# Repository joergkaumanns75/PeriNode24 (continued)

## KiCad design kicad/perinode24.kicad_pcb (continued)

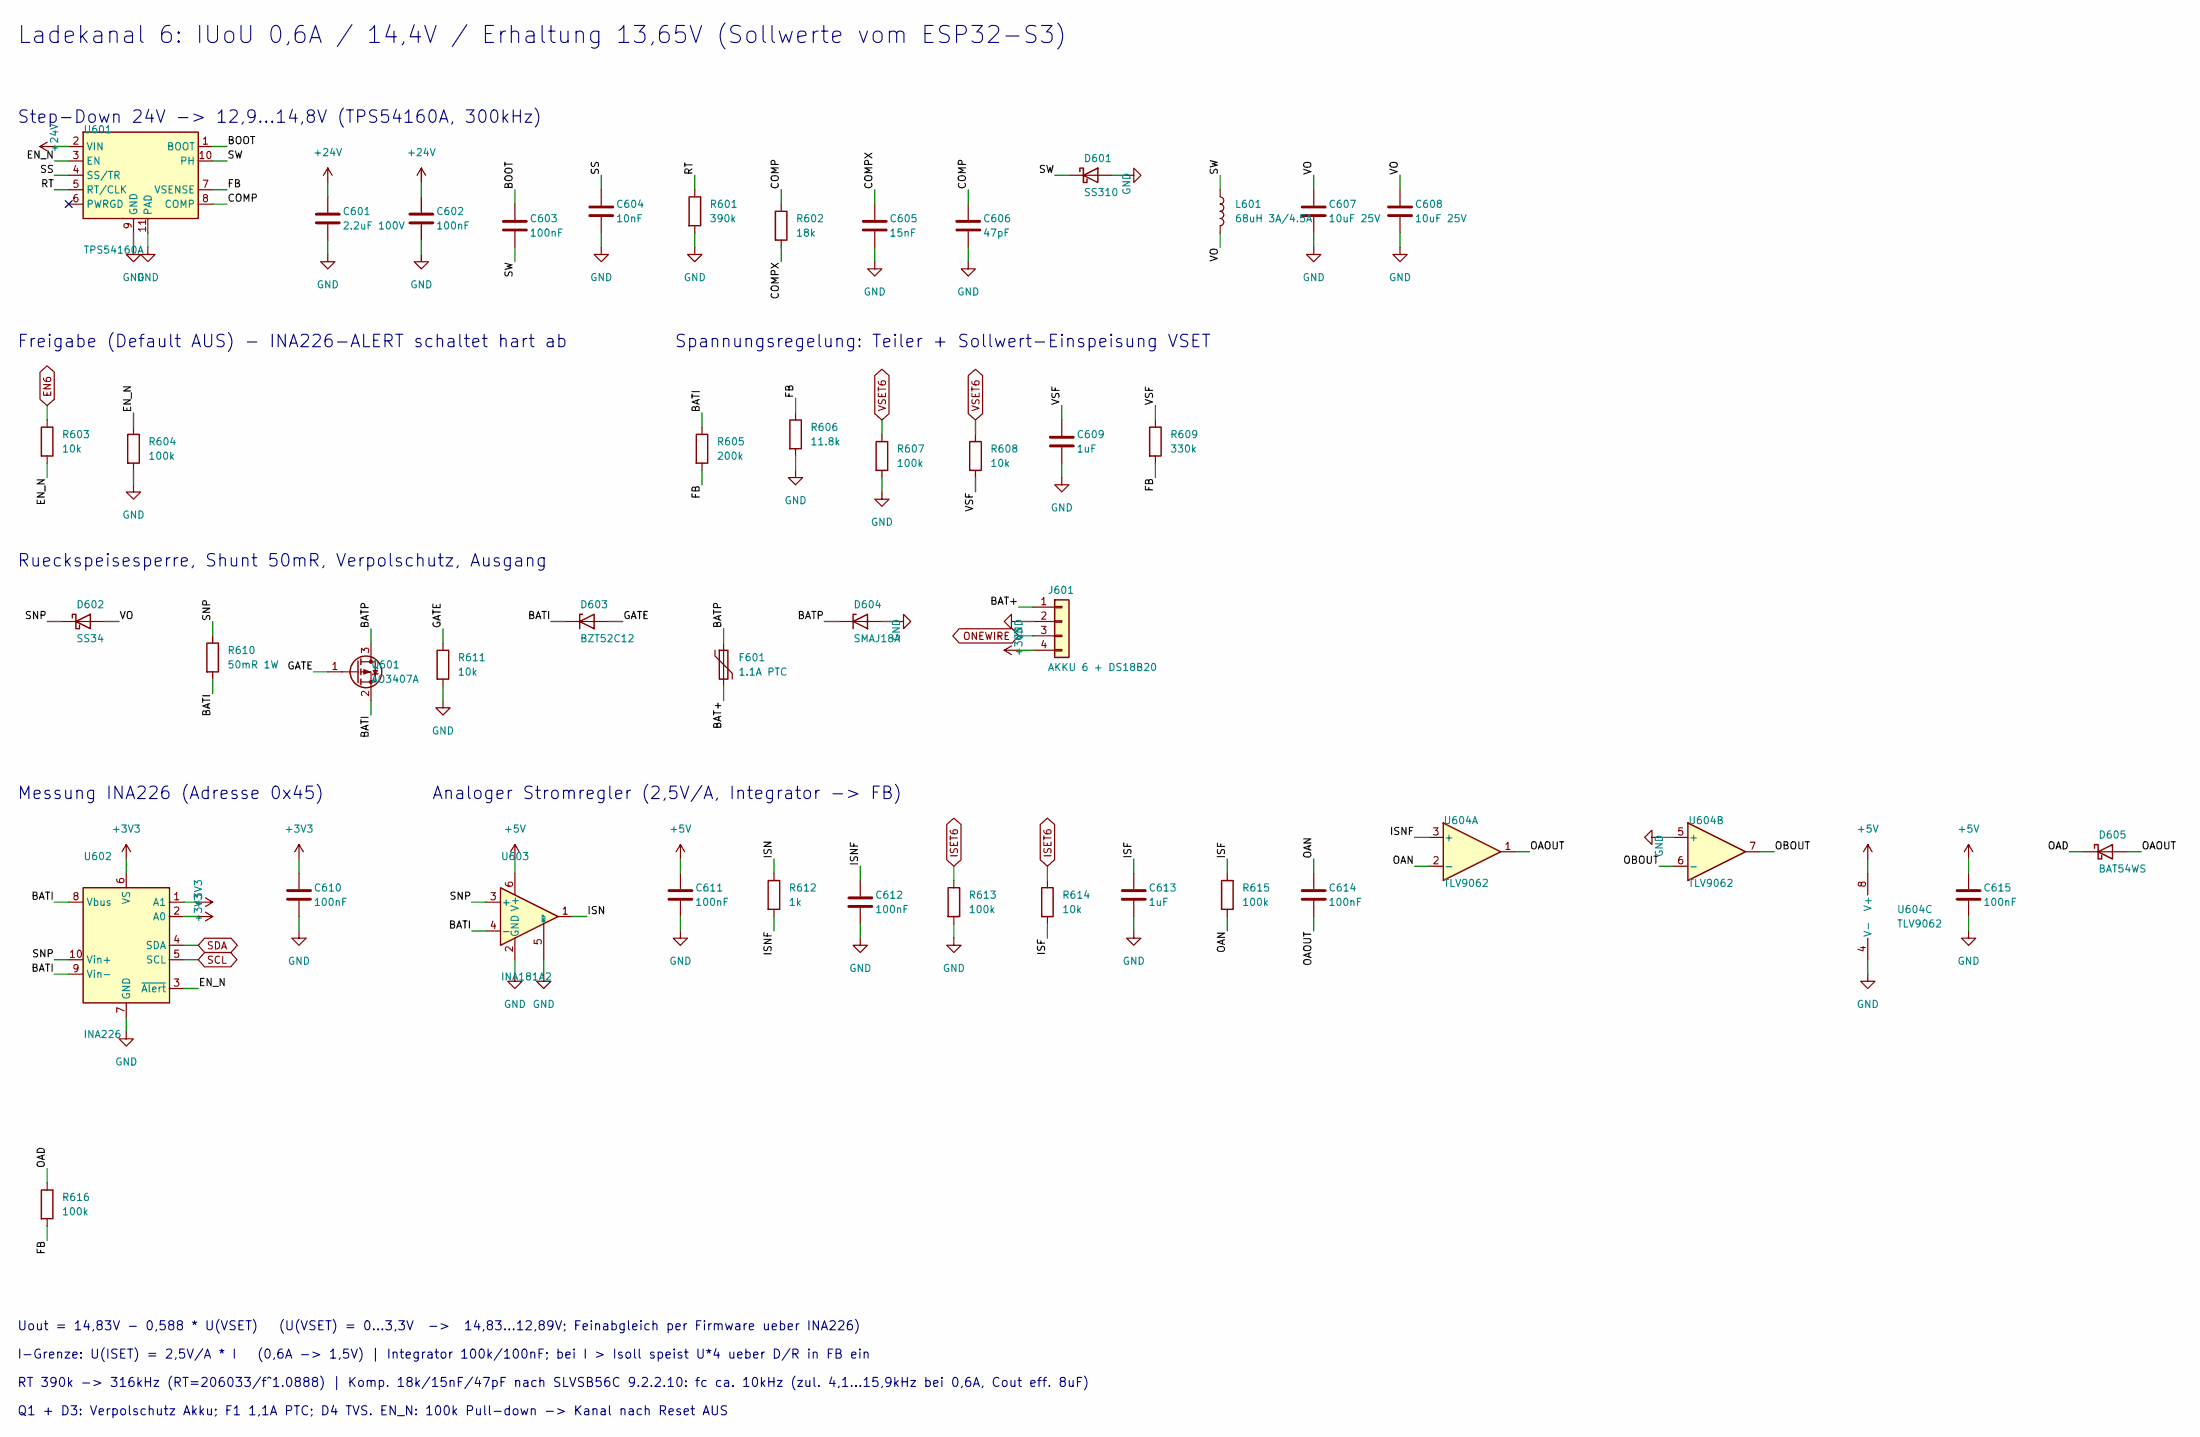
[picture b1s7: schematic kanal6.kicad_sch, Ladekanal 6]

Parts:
C601: 2.2uF 100V; C_1210_3225Metric; MPN CL32B225KCJSNNE; LCSC C55151
C602, C603, C610, C611, C612, C614, C615: 100nF; C_0603_1608Metric; MPN CC0603KRX7R9BB104; LCSC C14663
C604: 10nF; C_0603_1608Metric; MPN 0603B103K500NT; LCSC C57112
C605: 15nF; C_0603_1608Metric; MPN 0603B153K500CT; LCSC C296018
C606: 47pF; C_0603_1608Metric; MPN 0603CG470J500NT; LCSC C1671
C607, C608: 10uF 25V; C_0805_2012Metric; MPN CL21A106KAYNNNE; LCSC C15850
C609, C613: 1uF; C_0603_1608Metric; MPN CL10A105KB8NNNC; LCSC C15849
D601: SS310; D_SMA; MPN SS310; LCSC C15874
D602: SS34; D_SMA; MPN SS34; LCSC C8678
D603: BZT52C12; D_SOD-123; MPN BZT52C12; LCSC C2891780
D604: SMAJ18A; D_SMA; MPN SMAJ18A; LCSC C148219
D605: BAT54WS; D_SOD-323; MPN BAT54WS; LCSC C3040452
F601: 1.1A PTC; Fuse_1812_4532Metric; MPN 1812L110/16DR; LCSC C142746
J601: AKKU 6 + DS18B20; JST_PH_S4B-PH-SM4-TB_1x04-1MP_P2.00mm_Horizontal; MPN S4B-PH-SM4-TB(LF)(SN); LCSC C265102
L601: 68uH 3A/4.5A; L_TaiTech_TMPC1265_13.5x12.5mm; MPN FXL1360-680-M; LCSC C526032
Q601: AO3407A; SOT-23; MPN AO3407A; LCSC C15155
R601: 390k; R_0603_1608Metric; MPN 0603WAF3903T5E; LCSC C23150
R602: 18k; R_0603_1608Metric; MPN 0603WAF1802T5E; LCSC C25810
R603, R608, R611, R614: 10k; R_0603_1608Metric; MPN 0603WAF1002T5E; LCSC C25804
R604, R607, R613, R615, R616: 100k; R_0603_1608Metric; MPN 0603WAF1003T5E; LCSC C25803
R605: 200k; R_0603_1608Metric; MPN 0603WAF2003T5E; LCSC C25811
R606: 11.8k; R_0603_1608Metric; MPN RMC060311.8K1%N; LCSC C325665
R609: 330k; R_0603_1608Metric; MPN 0603WAF3303T5E; LCSC C23137
R610: 50mR 1W; R_1206_3216Metric; MPN RLM12FTCMR050; LCSC C912768
R612: 1k; R_0603_1608Metric; MPN 0603WAF1001T5E; LCSC C21190
U601: TPS54160A; MSOP-10-1EP_3x3mm_P0.5mm_EP1.68x1.88mm_ThermalVias; MPN TPS54160ADGQR; LCSC C390949
U602: INA226; VSSOP-10_3x3mm_P0.5mm; MPN INA226AIDGSR; LCSC C49851
U603: INA181A2; SOT-23-6; MPN INA181A2IDBVR; LCSC C2058784
U604: TLV9062; SOIC-8_3.9x4.9mm_P1.27mm; MPN TLV9062IDR; LCSC C398355

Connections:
+3V3: C610.1, J601.4, U602.1 (A1), U602.2 (A0), U602.6 (VS); also elsewhere on the board
+5V: C611.1, C615.1, U603.6 (V+), U604.8 (V+); also elsewhere on the board
+24V: C601.1, C602.1, U601.2 (VIN); also elsewhere on the board
/Ladekanal 6/BAT+: F601.2, J601.1
/Ladekanal 6/BATI: D603.1 (K), Q601.2 (S), R605.1, R610.2, U602.8 (Vbus), U602.9 (Vin-), U603.4 (-)
/Ladekanal 6/BATP: D604.1 (K), F601.1, Q601.3 (D)
/Ladekanal 6/BOOT: C603.1, U601.1 (BOOT)
/Ladekanal 6/COMP: C606.1, R602.1, U601.8 (COMP)
/Ladekanal 6/COMPX: C605.1, R602.2
/Ladekanal 6/EN_N: R603.2, R604.1, U601.3 (EN), U602.3 (~Alert)
/Ladekanal 6/FB: R605.2, R606.1, R609.2, R616.2, U601.7 (VSENSE)
/Ladekanal 6/GATE: D603.2 (A), Q601.1 (G), R611.1
/Ladekanal 6/ISF: C613.1, R614.2, R615.1
/Ladekanal 6/ISN: R612.1, U603.1
/Ladekanal 6/ISNF: C612.1, R612.2, U604.3 (+)
/Ladekanal 6/OAD: D605.1 (K), R616.1
/Ladekanal 6/OAN: C614.1, R615.2, U604.2 (-)
/Ladekanal 6/OAOUT: C614.2, D605.2 (A), U604.1
/Ladekanal 6/OBOUT: U604.6 (-), U604.7
/Ladekanal 6/RT: R601.1, U601.5 (RT/CLK)
/Ladekanal 6/SNP: D602.1 (K), R610.1, U602.10 (Vin+), U603.3 (+)
/Ladekanal 6/SS: C604.1, U601.4 (SS/TR)
/Ladekanal 6/SW: C603.2, D601.1 (K), L601.1, U601.10 (PH)
/Ladekanal 6/VO: C607.1, C608.1, D602.2 (A), L601.2
/Ladekanal 6/VSF: C609.1, R608.2, R609.1
EN6: R603.1; also elsewhere on the board
GND: C601.2, C602.2, C604.2, C605.2, C606.2, C607.2, C608.2, C609.2, C610.2, C611.2, C612.2, C613.2, C615.2, D601.2 (A), D604.2 (A), J601.2, R601.2, R604.2, R606.2, R607.2, R611.2, R613.2, U601.9 (GND), U601.11 (PAD), U602.7 (GND), U603.2 (GND), U603.5 (REF), U604.4 (V-), U604.5 (+); also elsewhere on the board
ISET6: R613.1, R614.1; also elsewhere on the board
ONEWIRE: J601.3; also elsewhere on the board
SCL: U602.5 (SCL); also elsewhere on the board
SDA: U602.4 (SDA); also elsewhere on the board
VSET6: R607.1, R608.1; also elsewhere on the board

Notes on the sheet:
Ladekanal 6: IUoU 0,6A / 14,4V / Erhaltung 13,65V (Sollwerte vom ESP32-S3)
Step-Down 24V -> 12,9...14,8V (TPS54160A, 300kHz)
Freigabe (Default AUS) - INA226-ALERT schaltet hart ab
Spannungsregelung: Teiler + Sollwert-Einspeisung VSET
Rueckspeisesperre, Shunt 50mR, Verpolschutz, Ausgang
Messung INA226 (Adresse 0x45)
Analoger Stromregler (2,5V/A, Integrator -> FB)
Uout = 14,83V - 0,588 * U(VSET) (U(VSET) = 0...3,3V -> 14,83...12,89V; Feinabgleich per Firmware ueber INA226)
I-Grenze: U(ISET) = 2,5V/A * I (0,6A -> 1,5V) | Integrator 100k/100nF; bei I > Isoll speist U*4 ueber D/R in FB ein
RT 390k -> 316kHz (RT=206033/f^1.0888) | Komp. 18k/15nF/47pF nach SLVSB56C 9.2.2.10: fc ca. 10kHz (zul. 4,1...15,9kHz bei 0,6A, Cout eff. 8uF)
Q1 + D3: Verpolschutz Akku; F1 1,1A PTC; D4 TVS. EN_N: 100k Pull-down -> Kanal nach Reset AUS

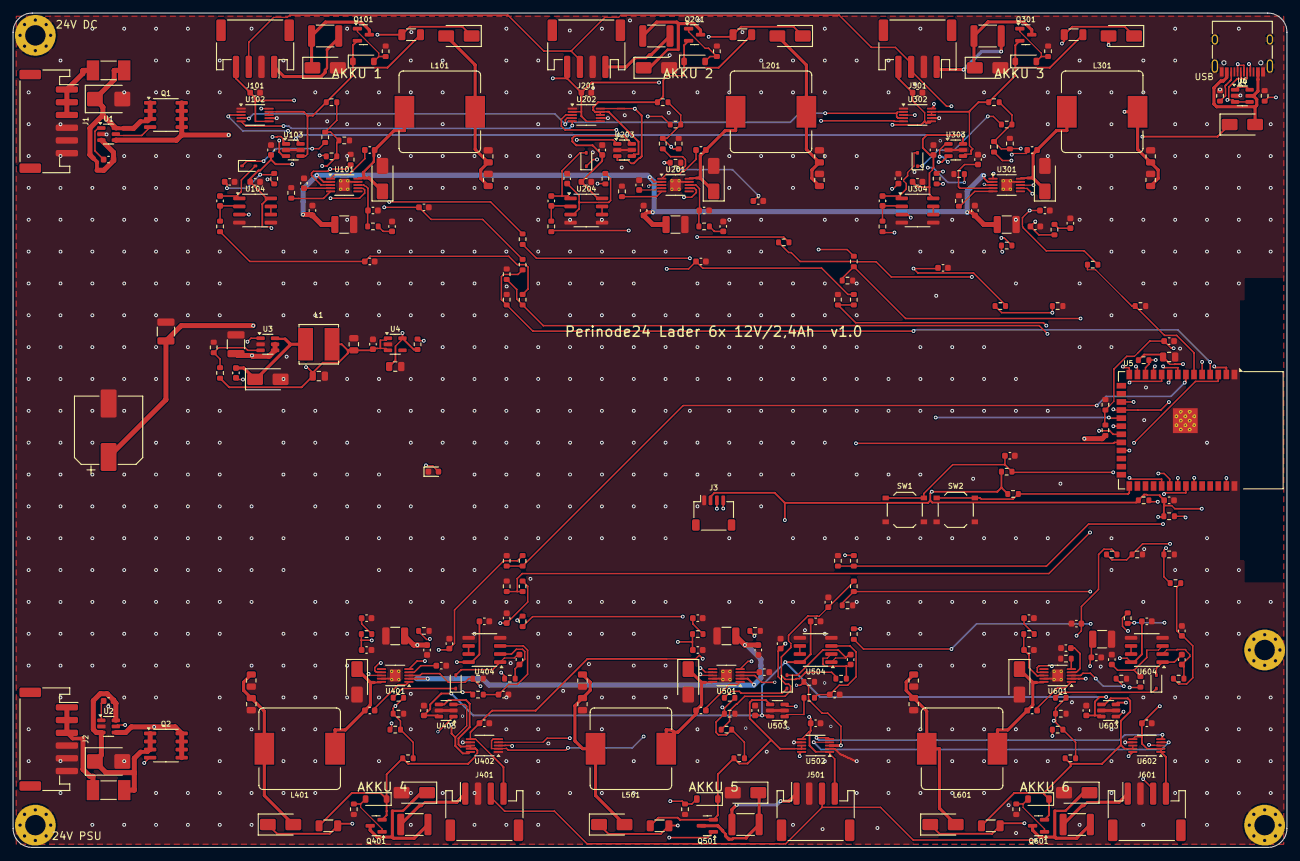
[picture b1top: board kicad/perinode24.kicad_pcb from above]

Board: 4 copper layers, 200.0 x 131.0 mm, 316 parts (0 on the bottom side), 177 nets.

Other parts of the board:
H1, H2, H3, H4: MountingHole_3.2mm_M3_Pad_Via

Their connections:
GND: H1.1, H2.1, H3.1, H4.1; also elsewhere on the board

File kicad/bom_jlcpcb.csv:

Comment,Designator,Footprint,LCSC Part #,MPN,Menge,LCSC geprueft
100nF,"C1,C2,C5,C7,C13,C102,C103,C110,C111,C112,C114,C115,C202,C203,C210,C211,C212,C214,C215,C302,C303,C310,C311,C312,C314,C315,C402,C403,C410,C411,C412,C414,C415,C502,C503,C510,C511,C512,C514,C515,C602,C603,C610,C611,C612,C614,C615",C_0603_1608Metric,C14663,CC0603KRX7R9BB104,47,ja
470uF 50V,C3,CP_Elec_10x12.5,C22469994,EFVM050ADA471M10C0,1,ja
2.2uF 100V,"C4,C6,C101,C201,C301,C401,C501,C601",C_1210_3225Metric,C55151,CL32B225KCJSNNE,8,ja
10uF 25V,"C8,C9,C11,C12,C107,C108,C207,C208,C307,C308,C407,C408,C507,C508,C607,C608",C_0805_2012Metric,C15850,CL21A106KAYNNNE,16,ja
1uF,"C10,C14,C109,C113,C209,C213,C309,C313,C409,C413,C509,C513,C609,C613",C_0603_1608Metric,C15849,CL10A105KB8NNNC,14,ja
10nF,"C104,C204,C304,C404,C504,C604",C_0603_1608Metric,C57112,0603B103K500NT,6,ja
15nF,"C105,C205,C305,C405,C505,C605",C_0603_1608Metric,C296018,0603B153K500CT,6,ja
47pF,"C106,C206,C306,C406,C506,C606",C_0603_1608Metric,C1671,0603CG470J500NT,6,NEIN
SMBJ33A,"D1,D2",D_SMB,C353366,SMBJ33A,2,ja
SS310,"D3,D101,D201,D301,D401,D501,D601",D_SMA,C15874,SS310,7,ja
LED gruen,D4,LED_0603_1608Metric,C72043,19-217/GHC-YR1S2/3T,1,ja
SS34,"D5,D102,D202,D302,D402,D502,D602",D_SMA,C8678,SS34,7,ja
BZT52C12,"D103,D203,D303,D403,D503,D603",D_SOD-123,C2891780,BZT52C12,6,ja
SMAJ18A,"D104,D204,D304,D404,D504,D604",D_SMA,C148219,SMAJ18A,6,ja
BAT54WS,"D105,D205,D305,D405,D505,D605",D_SOD-323,C3040452,BAT54WS,6,ja
5A T,"F1,F2",Fuse_Littelfuse-NANO2-451_453,C66503,0452005.MRL,2,ja
1.1A PTC,"F101,F201,F301,F401,F501,F601",Fuse_1812_4532Metric,C142746,1812L110/16DR,6,ja
JST PH 6P SMD,"J1,J2",JST_PH_S6B-PH-SM4-TB_1x06-1MP_P2.00mm_Horizontal,C265405,S6B-PH-SM4-TB(LF)(SN),2,ja
Qwiic/OLED,J3,JST_SH_SM04B-SRSS-TB_1x04-1MP_P1.00mm_Horizontal,C160404,SM04B-SRSS-TB(LF)(SN),1,ja
USB-C,J4,USB_C_Receptacle_HRO_TYPE-C-31-M-12,C165948,TYPE-C-31-M-12,1,ja
JST PH 4P SMD,"J101,J201,J301,J401,J501,J601",JST_PH_S4B-PH-SM4-TB_1x04-1MP_P2.00mm_Horizontal,C265102,S4B-PH-SM4-TB(LF)(SN),6,ja
22uH 1.5A,L1,L_Bourns_SRN6045TA,C780213,SRN6045-220M,1,ja
68uH 3A/4.5A,"L101,L201,L301,L401,L501,L601",L_TaiTech_TMPC1265_13.5x12.5mm,C526032,FXL1360-680-M,6,ja
AO4264E,"Q1,Q2",SOIC-8_3.9x4.9mm_P1.27mm,C334232,AO4264E,2,ja
AO3407A,"Q101,Q201,Q301,Q401,Q501,Q601",SOT-23,C15155,AO3407A,6,ja
100k,"R1,R3,R104,R107,R113,R115,R116,R204,R207,R213,R215,R216,R304,R307,R313,R315,R316,R404,R407,R413,R415,R416,R504,R507,R513,R515,R516,R604,R607,R613,R615,R616",R_0603_1608Metric,C25803,0603WAF1003T5E,32,ja
10k,"R2,R6,R7,R103,R108,R111,R114,R203,R208,R211,R214,R303,R308,R311,R314,R403,R408,R411,R414,R503,R508,R511,R514,R603,R608,R611,R614",R_0603_1608Metric,C25804,0603WAF1002T5E,27,ja
18k,"R4,R102,R202,R302,R402,R502,R602",R_0603_1608Metric,C25810,0603WAF1802T5E,7,ja
1k,"R5,R112,R212,R312,R412,R512,R612",R_0603_1608Metric,C21190,0603WAF1001T5E,7,ja
2.2k,"R8,R9",R_0603_1608Metric,C4190,0603WAF2201T5E,2,ja
4.7k,R10,R_0603_1608Metric,C23162,0603WAF4701T5E,1,ja
5.1k,"R11,R12",R_0603_1608Metric,C23186,0603WAF5101T5E,2,ja
390k,"R101,R201,R301,R401,R501,R601",R_0603_1608Metric,C23150,0603WAF3903T5E,6,ja
200k,"R105,R205,R305,R405,R505,R605",R_0603_1608Metric,C25811,0603WAF2003T5E,6,ja
11.8k,"R106,R206,R306,R406,R506,R606",R_0603_1608Metric,C325665,RMC060311.8K1%N,6,ja
330k,"R109,R209,R309,R409,R509,R609",R_0603_1608Metric,C23137,0603WAF3303T5E,6,ja
50mR 1W,"R110,R210,R310,R410,R510,R610",R_1206_3216Metric,C912768,RLM12FTCMR050,6,ja
TS-1187A,"SW1,SW2",SW_Push_1P1T_XKB_TS-1187A,C318884,TS-1187A-B-A-B,2,ja
LM74700-Q1,"U1,U2",SOT-23-6,C2941042,LM74700QDBVRQ1,2,ja
LMR16006X,U3,TSOT-23-6,C2070731,LMR16006XDDCT,1,ja
TLV75733P,U4,SOT-23-5,C485517,TLV75733PDBVR,1,ja
ESP32-S3-WROOM-1-N8R8,U5,ESP32-S3-WROOM-1,C2913201,ESP32-S3-WROOM-1-N8R8,1,ja
USBLC6-2SC6,U6,SOT-23-6,C7519,USBLC6-2SC6,1,ja
TPS54160A,"U101,U201,U301,U401,U501,U601",MSOP-10-1EP_3x3mm_P0.5mm_EP1.68x1.88mm_ThermalVias,C390949,TPS54160ADGQR,6,ja
INA226,"U102,U202,U302,U402,U502,U602",VSSOP-10_3x3mm_P0.5mm,C49851,INA226AIDGSR,6,ja
INA181A2,"U103,U203,U303,U403,U503,U603",SOT-23-6,C2058784,INA181A2IDBVR,6,ja
TLV9062,"U104,U204,U304,U404,U504,U604",SOIC-8_3.9x4.9mm_P1.27mm,C398355,TLV9062IDR,6,ja

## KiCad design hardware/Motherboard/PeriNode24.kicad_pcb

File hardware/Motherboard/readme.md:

# PeriNode24 – Motherboard

KiCad-Projekt der PeriNode24-Hauptplatine (ESP32-S3, RFM69HW, 24 Zündkanäle).

| Datei | Inhalt |
|---|---|
| `PeriNode24.kicad_pro` | KiCad-Projekt (hiermit öffnen) |
| `PeriNode24.kicad_sch` | Schaltplan |
| `PeriNode24.kicad_pcb` | Platinenlayout |
| `PeriNode24.pdf` | Schaltplan als PDF |
| `fabrication-toolkit-options.json` | Einstellungen für das Fabrication-Toolkit-Plugin (JLCPCB) |

Verwendet nur KiCad-Standardbibliotheken sowie die Espressif-Bibliothek (Plugin- und Content-Manager).
Lokale Dateien wie `*.kicad_prl`, `fp-info-cache`, Backups und Freerouting-Dateien werden über `hardware/.gitignore` ausgeschlossen.

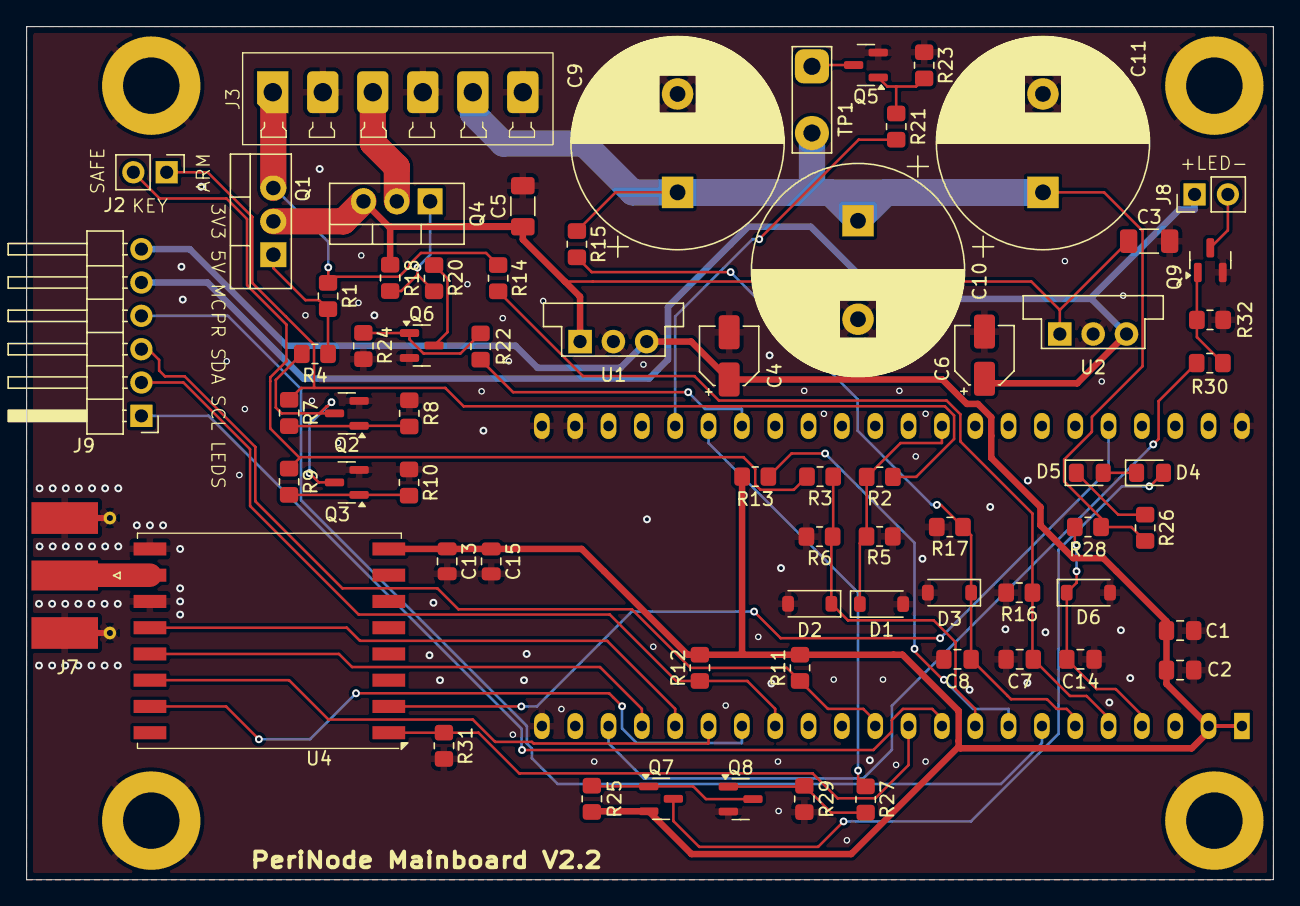
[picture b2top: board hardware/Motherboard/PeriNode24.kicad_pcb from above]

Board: 2 copper layers, 95.0 x 65.0 mm, 74 parts (1 on the bottom side), 46 nets.

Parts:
C1, C7, C8, C14: 100n; C_0805_2012Metric_Pad1.18x1.45mm_HandSolder
C2: 22uF/10V; C_0805_2012Metric_Pad1.18x1.45mm_HandSolder
C3, C5: 10uF 50V; C_1206_3216Metric_Pad1.33x1.80mm_HandSolder
C4, C6: 22uF 10V; CP_Elec_4x5.8
C9, C10, C11: 1000uF 63V; CP_Radial_D16.0mm_P7.50mm
C13: 100n; C_0805_2012Metric
C15: 10u; C_0805_2012Metric
D1, D2, D3, D6: 3V3; D_SOD-123
D4, D5: 4148; D_0805_2012Metric_Pad1.15x1.40mm_HandSolder
H1, H2, H3, H4: MTHole; MountingHole_4.3mm_M4_DIN965_Pad
J2: KEYSWITCH; PinHeader_1x02_P2.54mm_Vertical
J3: PowerTerminal; 6 Pin__15EDGVC-3.81
J7: SMA; SMA_Molex_73251-1153_EdgeMount_Horizontal
J8: ARM_LED_OUTPUT; PinHeader_1x02_P2.54mm_Vertical
J9: PowerTerminal; PinHeader_1x06_P2.54mm_Horizontal
Q1, Q4: IRF4905; TO-220-3_Vertical
Q2, Q3, Q6, Q8, Q9: 2N7002K; SOT-23
Q5: NDS 355; SOT-23
Q7: BSS84; SOT-23
R1, R18: 47K; R_0805_2012Metric_Pad1.20x1.40mm_HandSolder
R2, R3: 3K3; R_0805_2012Metric_Pad1.20x1.40mm_HandSolder
R4, R5, R6, R11, R12, R20: 4K7; R_0805_2012Metric_Pad1.20x1.40mm_HandSolder
R7, R8, R9, R10, R13, R23, R24, R25, R28, R29, R31, R32: 10K; R_0805_2012Metric_Pad1.20x1.40mm_HandSolder
R14, R15: 82K; R_0805_2012Metric_Pad1.20x1.40mm_HandSolder
R16: 9K1; R_0805_2012Metric_Pad1.20x1.40mm_HandSolder
R17: 820; R_0805_2012Metric_Pad1.20x1.40mm_HandSolder
R21, R22, R27, R30: 220; R_0805_2012Metric_Pad1.20x1.40mm_HandSolder
R26: 180; R_0805_2012Metric_Pad1.20x1.40mm_HandSolder
TP1: SolderPoint; TestPoint_2Pads_Pitch5.08mm_Drill1.3mm
U1: OKI-78SR-3.3/1.5-W36-C; Converter_DCDC_Murata_OKI-78SR_Vertical
U2: OKI-78SR-5_1.5-W36-C; Converter_DCDC_Murata_OKI-78SR_Vertical
U3: ESP32-S3-DevKitC
U4: RFM69HW; HOPERF_RFM69HW

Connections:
+3.3V: C1.1, C2.1, C4.1, C13.1, C15.1, J9.6, Q7.2 (S), R11.2, R12.2, R13.1, R25.1, U1.3 (OUT), U3.1 (3V3), U3.2 (3V3), U4.8 (3.3V)
+5V: C6.1, J8.1, J9.5, U2.3 (OUT)
+12V: J3.1, Q1.3 (S), R1.1, R14.1
/CHANNEL_LEDS: J9.1, U3.10 (GPIO17/ADC2_CH6)
/Discharge_C_Ign: R21.1, U3.27 (GPIO21)
/ENABLE_WIFI: R13.2, U3.8 (GPIO15/ADC2_CH4/32K_P)
/IN_ARMED_MODE: D1.1 (K), R2.2, R5.1, U3.35 (GPIO38)
/IN_SAFE_MODE: D2.1 (K), R3.2, R6.1, U3.9 (GPIO16/ADC2_CH5/32K_N)
/LED_ARMED: R30.1, U3.20 (GPIO14/ADC2_CH3)
/LED_MINUS: J8.2, Q9.3 (D)
/MCP_RESET: J9.4, U3.7 (GPIO7/ADC1_CH6)
/MISO: U3.19 (GPIO13/ADC2_CH2), U4.13 (MISO)
/MODE_ARMED: R22.1, U3.29 (GPIO48)
/MODE_TEST: R27.1, U3.28 (GPIO47)
/MOSI: U3.17 (GPIO11/ADC2_CH0), U4.14 (MOSI)
/RFM69_INT: U3.40 (GPIO2/ADC1_CH1), U4.2 (DIO0)
/RFM_RESET: R31.1, U3.11 (GPIO18/ADC2_CH7), U4.1 (RESET)
/RF_ANT: J7.1 (In), U4.10 (ANA)
/SCK: U3.18 (GPIO12/ADC2_CH1), U4.12 (SCK)
/SCL: J9.2, R12.1, U3.15 (GPIO9/ADC1_CH8)
/SDA: J9.3, R11.1, U3.12 (GPIO8/ADC1_CH7)
/SS: U3.16 (GPIO10/ADC1_CH9), U4.15 (NSS)
/U_MESS_BATT: C7.2, R14.2, R16.1, U3.5 (GPIO5/ADC1_CH4)
/U_MESS_CHANNEL: C14.1, D6.1 (K), R28.1, U3.4 (GPIO4/ADC1_CH3)
/U_MESS_IGN: C8.2, D3.1 (K), R15.2, R17.1, U3.6 (GPIO6/ADC1_CH5)
/V_EIN: C3.1, C5.1, Q1.2 (D), Q4.3 (S), R18.1, U1.1 (IN), U2.1 (IN)
/V_Stepup: J3.3, Q4.2 (D)
GND: C1.2, C2.2, C3.2, C4.2, C5.2, C6.2, C7.1, C8.1, C9.2, C10.2, C11.2, C13.2, C14.2, C15.2, D1.2 (A), D2.2 (A), D3.2 (A), D6.2 (A), H1.1, H2.1, H3.1, H4.1, J3.2, J3.4, J3.6, J7.2 (Ext), Q2.2 (S), Q3.2 (S), Q5.2 (S), Q6.2 (S), Q8.2 (S), Q9.2 (S), R5.2, R6.2, R8.2, R10.1, R16.2, R17.2, R23.1, R24.1, R29.1, R31.2, R32.1, U1.2 (GND), U2.2 (GND), U3.22 (GND), U3.23 (GND), U3.24 (GND), U3.44 (GND), U4.9 (GND), U4.11 (GND)
unnamed: D4.2 (A), Q7.3 (D)
unnamed: D4.1 (K), D5.2 (A)
unnamed: D5.1 (K), R26.1
unnamed: Q1.1 (G), R1.2, R4.1
unnamed: Q2.3 (D), Q3.3 (D), R4.2
unnamed: Q2.1 (G), R7.2, R8.1
unnamed: Q3.1 (G), R9.2, R10.2
unnamed: Q4.1 (G), R18.2, R20.1
unnamed: Q5.3 (D), TP1.1
unnamed: Q5.1 (G), R21.2, R23.2
unnamed: Q6.3 (D), R20.2
unnamed: Q6.1 (G), R22.2, R24.2
unnamed: Q7.1 (G), Q8.3 (D), R25.2
unnamed: Q8.1 (G), R27.2, R29.2
unnamed: Q9.1 (G), R30.2, R32.2
ON_ARMED_MODE: J2.1, R2.1, R7.1
ON_SAFE_MODE: J2.2, R3.1, R9.1
U_IGN: C9.1, C10.1, C11.1, J3.5, R15.1, R26.2, R28.2, TP1.2

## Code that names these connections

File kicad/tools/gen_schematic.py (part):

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            pin("passive", 12.7, 5.08, 180, "BOOT", "1"),
            pin("output", 12.7, 2.54, 180, "PH", "10"),
            pin("input", 12.7, -2.54, 180, "VSENSE", "7"),
            pin("passive", 12.7, -5.08, 180, "COMP", "8"),
            pin("power_in", -1.27, -10.16, 90, "GND", "9"),
            pin("passive", 1.27, -10.16, 90, "PAD", "11")]]
    # N-MOSFET SO-8: Grafik von Device:Q_NMOS_GDS übernehmen
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    sh.cy = 32

    sh.group("Eingang 24V DC (18-32V) mit Verpolschutz / Ideal-Diode")
    sh.part("Connector_Generic:Conn_01x06", "J1", "PH6", {"1": "VIN_DC", "2": "VIN_DC", "3": "VIN_DC", "4": "GND", "5": "GND", "6": "GND"}, value="24V DC IN (3x+ / 3x-)")
    sh.F("F1", "F5A", "VIN_DC", "VIN_DC_F")
    sh.Z("D1", "TVS33", "VIN_DC_F", "GND")
    sh.part("Power_Management:LM74700", "U1", "LM74700",
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    sh.pwr_flag("VIN_DC_F")

    sh.group("Eingang Netzteil 24V (Mean Well LRS-100-24, 230/240V AC extern)")
    sh.part("Connector_Generic:Conn_01x06", "J2", "PH6", {"1": "VIN_PSU", "2": "VIN_PSU", "3": "VIN_PSU", "4": "GND", "5": "GND", "6": "GND"}, value="24V PSU IN (3x+ / 3x-)")
    sh.F("F2", "F5A", "VIN_PSU", "VIN_PSU_F")
    sh.Z("D2", "TVS33", "VIN_PSU_F", "GND")
    sh.part("Power_Management:LM74700", "U2", "LM74700",
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        "- 230/240V AC nur ueber zertifiziertes Netzteil (Mean Well LRS-100-24 bzw. HDR-100-24N) an J2 - keine Netzspannung auf dieser Platine.",
        "- J1 und J2 duerfen gleichzeitig angeschlossen sein (Ideal-Dioden-ODER U1/U2).",
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        "- GPIO: VSET1-6 = IO4,5,6,7,15,16 (LEDC) | ISET1-6 = IO17,18,21,38,39,40 (Sigma-Delta) | EN1-6 = IO11,12,13,14,41,42",
        "- I2C SDA IO8 / SCL IO9 | 1-Wire IO10 | Busspannung IO1 (Teiler 100k/10k) | USB IO19/IO20",
    ]
    for i, n in enumerate(notes):
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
